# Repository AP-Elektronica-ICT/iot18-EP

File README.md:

# Internet of Things - Logistiek Tracking (Naam WIP)

## Groepsleden
Geentjens Wim - Trackingsoftware developer  
Knaepkens Tom - Team leader + Trackinghardware developer  
Scheyltjens Yorick - Backend webdeveloper  
Cools Jens - Frontend webdeveloper  

## Documentatie

Leg hier de link naar de nuttige documentatie

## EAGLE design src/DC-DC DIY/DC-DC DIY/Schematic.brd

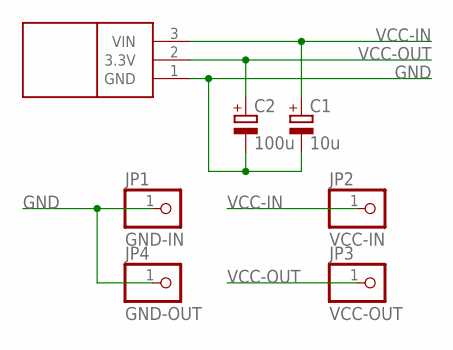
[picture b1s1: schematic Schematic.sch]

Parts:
C1: 10u; E2,5-7
C2: 100u; E3,5-8
JP1: GND-IN; 1X01
JP2: VCC-IN; 1X01
JP3: VCC-OUT; 1X01
JP4: GND-OUT; 1X01
U$1: LD33VHORIZONTAL; TO220

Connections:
GND: C1.-, C2.-, JP1.1, JP4.1, U$1.1 (GND)
VCC-IN: C1.+, JP2.1, U$1.3 (VIN)
VCC-OUT: C2.+, JP3.1, U$1.2 (3.3V)

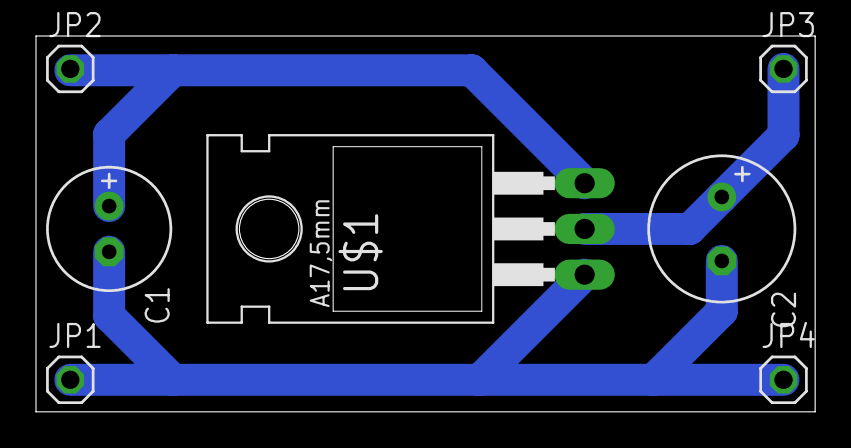
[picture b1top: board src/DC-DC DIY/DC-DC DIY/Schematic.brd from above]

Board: 2 copper layers, 43.3 x 20.9 mm, 7 parts (0 on the bottom side), 3 nets.

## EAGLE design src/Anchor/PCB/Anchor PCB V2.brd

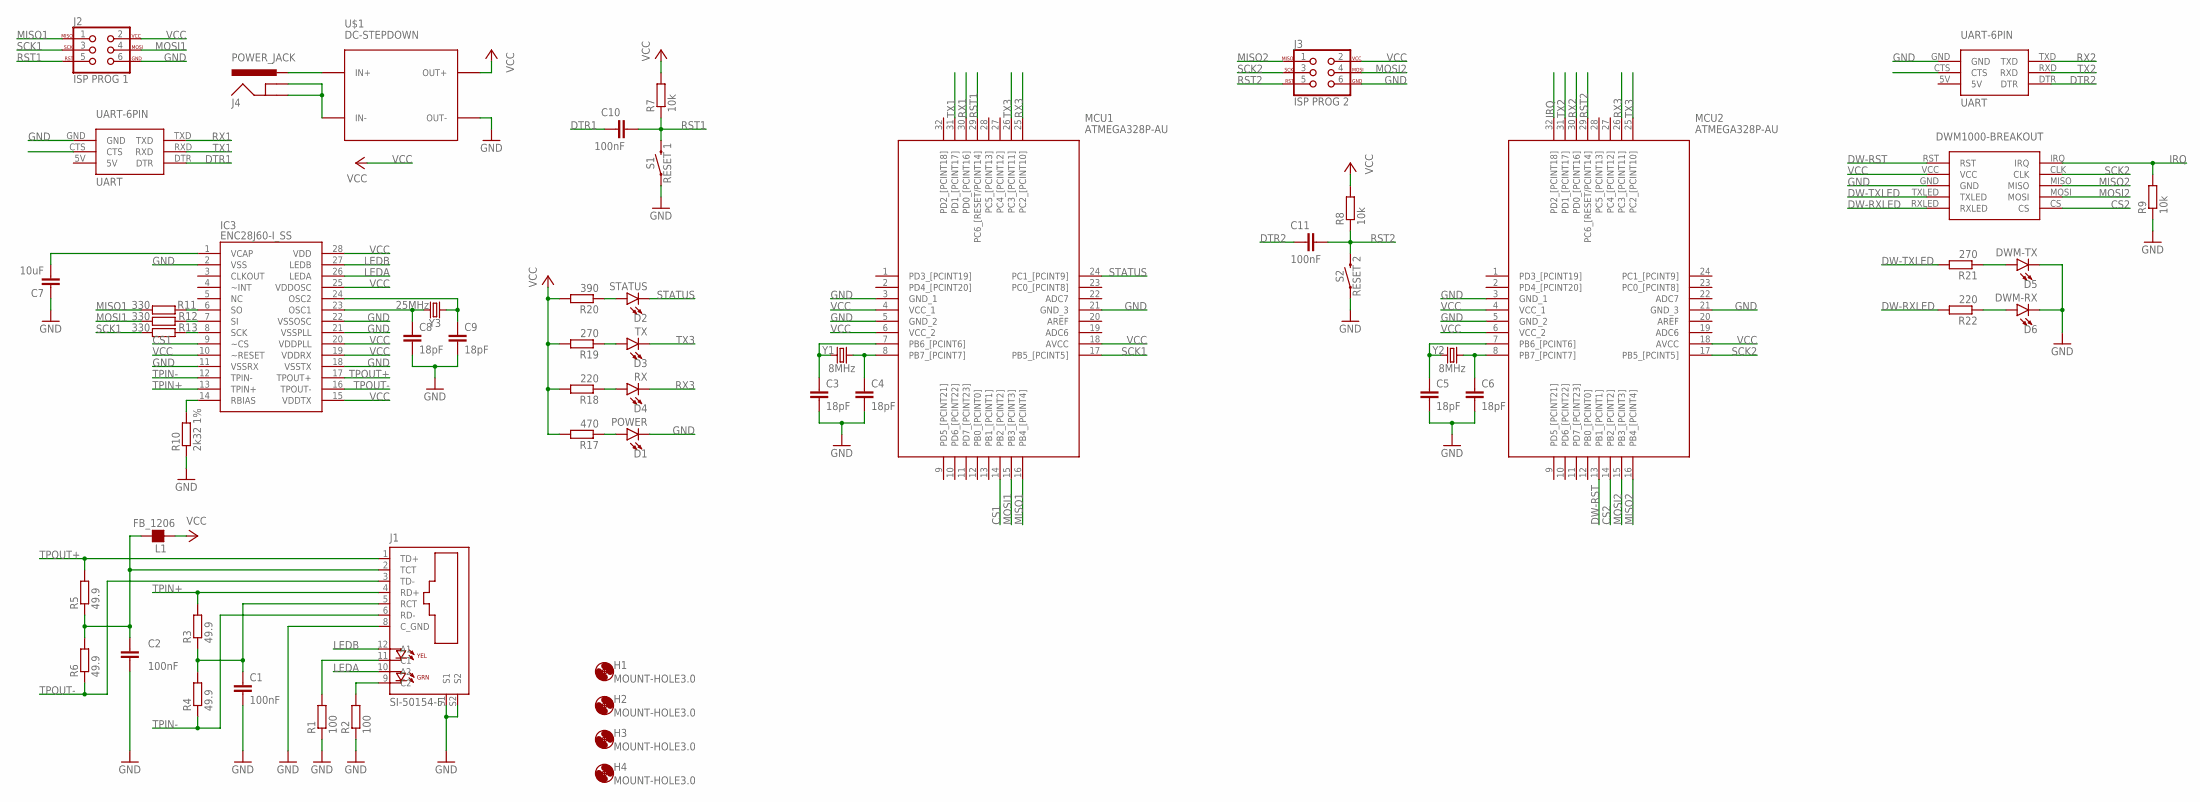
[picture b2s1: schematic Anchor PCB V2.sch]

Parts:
C1, C2, C10, C11: 100nF; C0805
C3, C4, C5, C6, C8, C9: 18pF; C0805
C7: 10uF; C0805
D1: POWER; LED-1206
D2: STATUS; LED-1206
D3: TX; LED-1206
D4: RX; LED-1206
D5: DWM-TX; LED-1206
D6: DWM-RX; LED-1206
H1, H2, H3, H4: MOUNT-HOLE3.0; 3,0
IC3: ENC28J60-I_SS; SOP65P780X200-28N
J1: SI-50154-F; STEWART_SI-50154-F
J2: ISP PROG 1; 2X3
J3: ISP PROG 2; 2X3
J4: POWER_JACK; POWER_JACK_PTH
L1: FB_1206; L1206
MCU1, MCU2: ATMEGA328P-AU; QFP80P900X900X120-32N
R1, R2: 100; R0805
R3, R4, R5, R6: 49.9; R1206
R7, R8, R9: 10k; R0805
R10: 2k32 1%; R1206
R11, R12, R13: 330; R0805
R17: 470; R1206
R18, R22: 220; R1206
R19, R21: 270; R1206
R20: 390; R1206
S1: RESET 1; TACTILE_SWITCH_PTH_6.0MM
S2: RESET 2; TACTILE_SWITCH_PTH_6.0MM
U$1: DC-STEPDOWN; DC-DC-STEP-DOWN-LM2596
U$2: DWM1000; DWM1000-BREAKOUT
UART1: UART1; UART-6PIN
UART2: UART2; UART-6PIN
Y1, Y2: 8MHz; HC49UP
Y3: 25MHz; HC49UP

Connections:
CS1: IC3.9 (~CS), MCU1.14 (PB2_[PCINT2])
CS2: MCU2.14 (PB2_[PCINT2]), U$2.CS
DTR1: C10.1, UART1.DTR
DTR2: C11.1, UART2.DTR
DW-RST: MCU2.13 (PB1_[PCINT1]), U$2.RST
DW-RXLED: R22.2, U$2.RXLED
DW-TXLED: R21.2, U$2.TXLED
GND: C1.2, C2.2, C3.2, C4.2, C5.2, C6.2, C7.1, C8.2, C9.2, D1.C, D5.C, D6.C, IC3.2 (VSS), IC3.11 (VSSRX), IC3.18 (VSSTX), IC3.21 (VSSPLL), IC3.22 (VSSOSC), J1.8 (C_GND), J1.S1, J1.S2, J2.6, J3.6, MCU1.3 (GND_1), MCU1.5 (GND_2), MCU1.21 (GND_3), MCU2.3 (GND_1), MCU2.5 (GND_2), MCU2.21 (GND_3), R1.1, R2.1, R9.1, R10.1, S1.1, S2.1, U$1.OUT-, U$2.GND, UART1.GND, UART2.GND
IN+: J4.PWR, U$1.IN+
IN-: J4.GND, J4.GNDBREAK, U$1.IN-
IRQ: MCU2.32 (PD2_[PCINT18]), R9.2, U$2.IRQ
LEDA: IC3.26 (LEDA), J1.10 (A2)
LEDB: IC3.27 (LEDB), J1.12 (A1)
MISO1: J2.1, MCU1.16 (PB4_[PCINT4]), R11.2
MISO2: J3.1, MCU2.16 (PB4_[PCINT4]), U$2.MISO
MOSI1: J2.4, MCU1.15 (PB3_[PCINT3]), R12.2
MOSI2: J3.4, MCU2.15 (PB3_[PCINT3]), U$2.MOSI
unnamed: J1.11 (C1), R1.2
unnamed: J1.9 (C2), R2.2
unnamed: C3.1, MCU1.7 (PB6_[PCINT6]), Y1.2
unnamed: C4.1, MCU1.8 (PB7_[PCINT7]), Y1.1
unnamed: C5.1, MCU2.7 (PB6_[PCINT6]), Y2.1
unnamed: C6.1, MCU2.8 (PB7_[PCINT7]), Y2.2
unnamed: C7.2, IC3.1 (VCAP)
unnamed: IC3.14 (RBIAS), R10.2
unnamed: C8.1, IC3.23 (OSC1), Y3.2
unnamed: C9.1, IC3.24 (OSC2), Y3.1
unnamed: IC3.6 (SO), R11.1
unnamed: C1.1, J1.5 (RCT), R3.1, R4.2
unnamed: C2.1, J1.2 (TCT), L1.2, R5.1, R6.2
unnamed: IC3.7 (SI), R12.1
unnamed: IC3.8 (SCK), R13.1
unnamed: D5.A, R21.1
unnamed: D4.A, R18.1
unnamed: D2.A, R20.1
unnamed: D3.A, R19.1
unnamed: D6.A, R22.1
unnamed: D1.A, R17.1
RST1: C10.2, J2.5, MCU1.29 (PC6_[RESET/PCINT14]), R7.1, S1.3 (2)
RST2: C11.2, J3.5, MCU2.29 (PC6_[RESET/PCINT14]), R8.1, S2.3 (2)
RX1: MCU1.30 (PD0_[PCINT16]), UART1.TXD
RX2: MCU2.30 (PD0_[PCINT16]), UART2.TXD
RX3: D4.C, MCU1.25 (PC2_[PCINT10]), MCU2.26 (PC3_[PCINT11])
SCK1: J2.3, MCU1.17 (PB5_[PCINT5]), R13.2
SCK2: J3.3, MCU2.17 (PB5_[PCINT5]), U$2.CLK
STATUS: D2.C, MCU1.24 (PC1_[PCINT9])
TPIN+: IC3.13 (TPIN+), J1.4 (RD+), R3.2
TPIN-: IC3.12 (TPIN-), J1.6 (RD-), R4.1
TPOUT+: IC3.17 (TPOUT+), J1.1 (TD+), R5.2
TPOUT-: IC3.16 (TPOUT-), J1.3 (TD-), R6.1
TX1: MCU1.31 (PD1_[PCINT17]), UART1.RXD
TX2: MCU2.31 (PD1_[PCINT17]), UART2.RXD
TX3: D3.C, MCU1.26 (PC3_[PCINT11]), MCU2.25 (PC2_[PCINT10])
VCC: IC3.10 (~RESET), IC3.15 (VDDTX), IC3.19 (VDDRX), IC3.20 (VDDPLL), IC3.25 (VDDOSC), IC3.28 (VDD), J2.2, J3.2, L1.1, MCU1.4 (VCC_1), MCU1.6 (VCC_2), MCU1.18 (AVCC), MCU2.4 (VCC_1), MCU2.6 (VCC_2), MCU2.18 (AVCC), R7.2, R8.2, R17.2, R18.2, R19.2, R20.2, U$1.OUT+, U$2.VCC

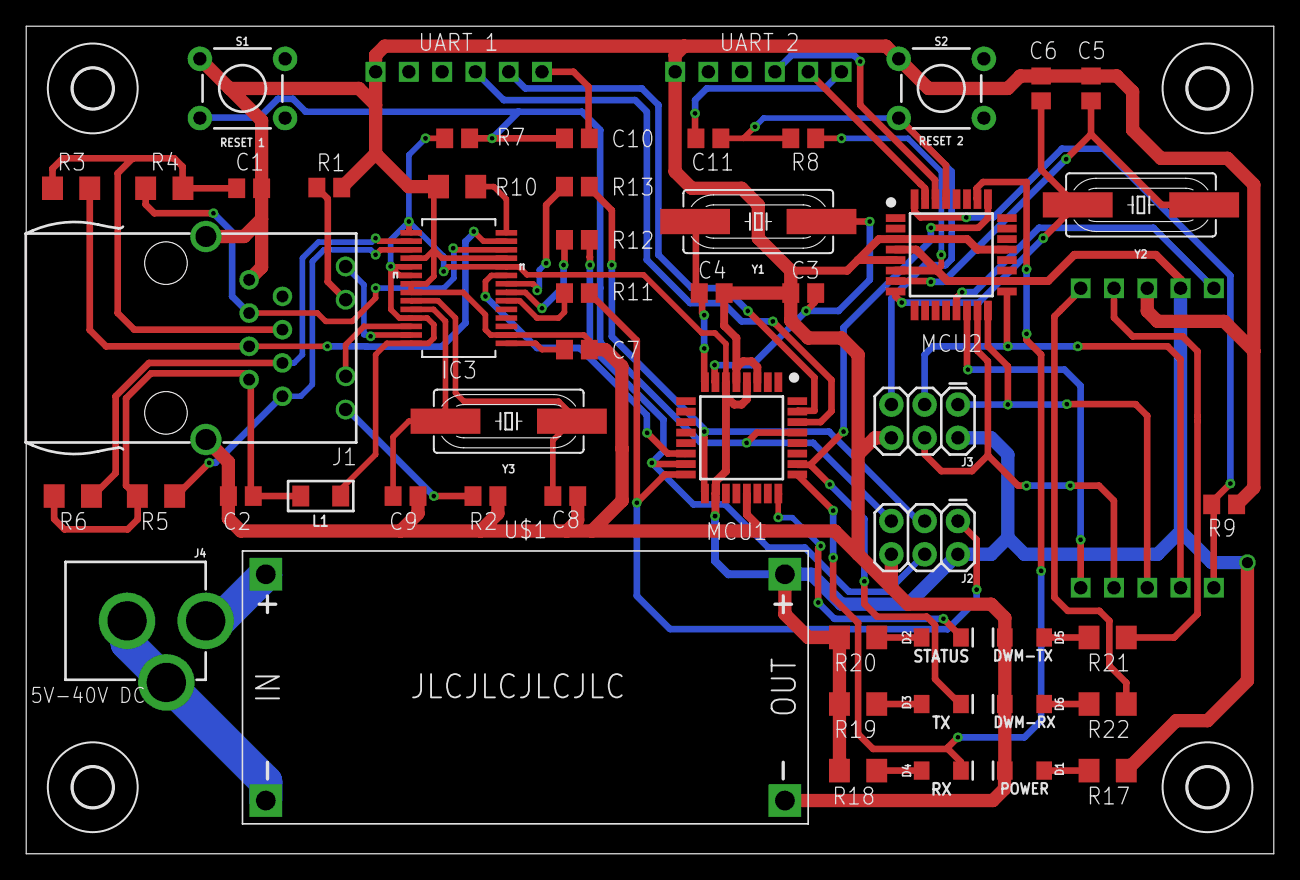
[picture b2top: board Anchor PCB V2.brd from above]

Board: 2 copper layers, 95.2 x 63.2 mm, 57 parts (0 on the bottom side), 54 nets.

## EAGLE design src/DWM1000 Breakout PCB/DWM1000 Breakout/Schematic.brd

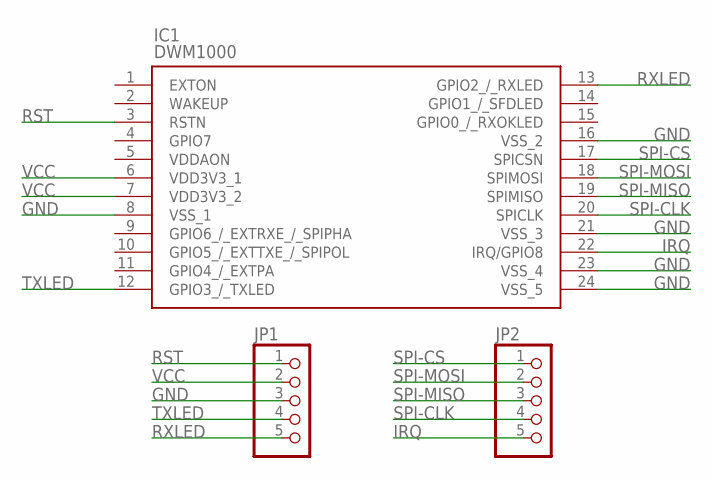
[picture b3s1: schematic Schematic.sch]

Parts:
IC1: DWM1000
JP1, JP2: PINHD-1X5; 1X05

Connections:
GND: IC1.8 (VSS_1), IC1.16 (VSS_2), IC1.21 (VSS_3), IC1.23 (VSS_4), IC1.24 (VSS_5), JP1.3
IRQ: IC1.22 (IRQ/GPIO8), JP2.5
RST: IC1.3 (RSTN), JP1.1
RXLED: IC1.13 (GPIO2_/_RXLED), JP1.5
SPI-CLK: IC1.20 (SPICLK), JP2.4
SPI-CS: IC1.17 (SPICSN), JP2.1
SPI-MISO: IC1.19 (SPIMISO), JP2.3
SPI-MOSI: IC1.18 (SPIMOSI), JP2.2
TXLED: IC1.12 (GPIO3_/_TXLED), JP1.4
VCC: IC1.6 (VDD3V3_1), IC1.7 (VDD3V3_2), JP1.2

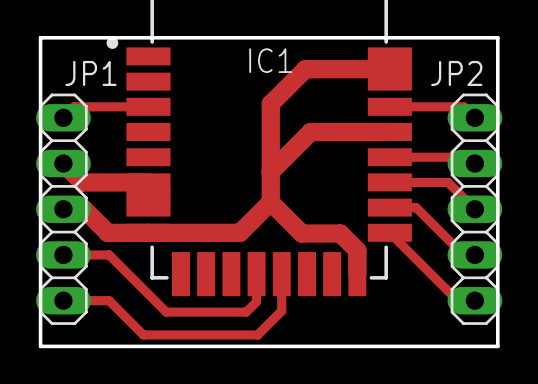
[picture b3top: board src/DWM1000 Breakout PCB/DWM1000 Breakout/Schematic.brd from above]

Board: 2 copper layers, 25.4 x 17.1 mm, 3 parts (0 on the bottom side), 10 nets.

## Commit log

2018-09-27 Added motivation documents
2018-09-27 groepsleden en taakverdeling ingevuld
2018-09-27 testing image link in markdown
2018-09-27 added architecture schematics
2018-09-27 Added inventarisatie hardware/software
2018-09-27 Market Research
2018-09-27 layout fixes
2018-09-27 Added Fysiek Design and schematic product
2018-09-27 Flowchart
2018-09-27 Added info analyse.md
2018-09-27 Fixed info bugs
2018-10-01 Added remote desktop file
2018-10-01 Started Angular Project
2018-10-01 Added routing
2018-10-02 Added map layout
2018-10-04 Added tag view in map
2018-10-05 Added Hardware Flowchart
2018-10-05 Moved motivation documents
2018-10-05 Added gitignore
2018-10-05 Added EtherCard library
2018-10-05 Created Anchor PCB Schematic
2018-10-05 Add Server
2018-10-06 Added Service Provider
2018-10-08 Added Coordinates Model
2018-10-08 Added Measurements Model
2018-10-08 Fixed bug in app.component
2018-10-08 Added DWM1000 Library
2018-10-08 Positioning testing
2018-10-08 Added Test data
2018-10-08 Added second login page
2018-10-08 Bug fix
2018-10-08 Git Bugfix
2018-10-08 Git merge conflicten
2018-10-08 Added mapview and tagview
2018-10-11 Added AllowAllMethods
2018-10-11 Added MeasurementController
2018-10-11 Breakout PCB added
2018-10-11 Anchor software V1 added
2018-10-11 Added V1 tag sketch (send id with data)
2018-10-12 Added hovering
2018-10-15 Added 'Stroke' to coordinatemodel
2018-10-15 Anchor software V2 added
2018-10-15 Added connection to database
2018-10-17 SQL issue solved
2018-10-17 Finished hovering
2018-10-18 Anchor schematic V1 screenshot added
2018-10-18 Add Tags model
2018-10-18 Add Anchors Model
2018-10-18 Fixed bugs in hovering -> finished
2018-10-18 Changed program from dummie data to real data
2018-10-18 Added Anchor and Tag Controller
2018-10-22 Added tag page
2018-10-23 Added .gitignore
2018-10-23 .gitignore fix
2018-10-23 .gitignore fix 2.0
2018-10-24 Added delete Tag api
2018-10-24 Added delete anchor api
2018-10-24 Moved a few charts
2018-10-24 Deleted unnecessary PCB files
2018-10-24 Added component libraries
2018-10-24 Added full component list/inventory
2018-10-24 Edited Anchor PCB schematic + Board V1
2018-10-24 Added TCP & UDP test sketches
2018-10-24 Added new version of Anchor sketch
2018-10-27 Removed some unnecessary resistors in Anchor V2
2018-10-27 Added Tag PCB V1
2018-10-27 Moved Eagle libraries to central location
2018-10-27 Removed unnecessary resistors from component list
2018-11-09 Tag lijst toegevoegd home page
2018-11-12 Uploud map en map view toegevoegd
2018-11-14 Timer toegevoegd
2018-11-14 PCB JLC tag added
2018-11-14 Hover bug fixed
2018-11-14 Tag case added
2018-11-14 Slider added
2018-11-14 Moved Tag PCB to 0,0
2018-11-19 Delay request slider changed
2018-11-19 Add New database migrations with Azure
2018-11-19 Name change in model
2018-11-19 Added Description field to TagModel
2018-11-19 User Model Added
2018-11-22 Add map row to User
2018-11-22 Map opload API added
2018-11-22 MeasurementModel name changed
2018-11-22 Added Detailpage for measurements
2018-11-22 RasPi files - Basic gateway functions
2018-11-25 Global Model Update
2018-11-25 Auto stash before merge of "master" and "origin/master"
2018-11-25 Add Migration
2018-11-25 Added UserController
2018-11-25 Added Timestamp to measurements
2018-11-25 Added Coordinates class
2018-11-26 Changed Height to Length in MapModel
2018-11-26 Partlist changed + added seperate Anchor sketches
2018-11-27 Changed map size
2018-11-28 Working version
2018-11-28 Native navbar
2018-11-28 Native map
2018-12-03 Backup commit
2018-12-08 DC-DC Breakout board created
2018-12-08 Updated partlist Tag
2018-12-08 Added serial parsing
2018-12-08 Added all code in new project MCU2
2018-12-08 Updated partlist Anchor
2018-12-08 Deleted CTS pin
2018-12-08 Changed baudrate
2018-12-09 Userstory IOT18EP-50
2018-12-10 Updated .gitignore
2018-12-10 Added Algorithm (again)
2018-12-10 Added api for deleting a tag
2018-12-10 Added api for adding a tag
2018-12-10 Added api for editing the description of a tag
2018-12-10 Update commit
2018-12-10 Code aangepast naar real data
2018-12-19 Update Tagcontroller so editing a tag is possible
2018-12-19 Update AnchorController so editing a anchor is possible
2018-12-19 Added floorplan to coordinates api
2018-12-19 changed interfaces
2018-12-20 Add map is now possible
2018-12-20 Add Anchor is now possible
2018-12-23 Timestamp on distance received
2018-12-23 Unix timestamp format
2018-12-23 MAC adress dynamisch gemaakt + meerdere anchors mogelijk
2018-12-23 Anchor case design V1 added
2018-12-23 Revert "MAC adress dynamisch gemaakt + meerdere anchors mogelijk"
    This reverts commit 795b303263730dc29949294aa32de9a3892c2424.
2018-12-23 MAC address dynamic
2018-12-27 Anchor case V2 added
2018-12-27 Tag case Sketchup files deleted
2019-01-03 Voorbereiding demo
2019-01-03 refresh changed
2019-01-03 Tag case + gateway case added
2019-01-03 Anchor calibration added
2019-01-03 DemoTagTrack
2019-01-04 Bug fix in Algorithm
2019-01-07 Multiple anchors added
2019-01-10 Added demo script
2019-01-10 demo ready
2019-01-10 Reset times changed
2019-01-11 filter toegevoegd
2019-01-11 Anchor 3 hard reset
2019-01-11 Add coordinates to tag model
2019-01-19 Changed map get and upload
2019-01-20 Added tag list
2019-01-21 Ethernet delay toegevoegd
2019-01-21 Plattegrond toegevoegd
2019-04-03 Raspberry Pi scripts toegevoegd
2019-04-03 Delay langer gemaakt
2019-04-03 Index file geupdate

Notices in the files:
parts and their libraries:
SparkFun-LED: Licensing: Creative Commons ShareAlike 4.0 International - https://creativecommons.org/licenses/by-sa/4.0
rc-master-smd: Copyright (C) 2007, Bob Starr
